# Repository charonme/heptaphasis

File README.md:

# [heptaphasis](http://charon.sk/heptaphasis)
### 7-phase quadrature sine LFO for eurorack
based on [Yusynth Quadrature VC-LFO](http://yusynth.net/Modular/EN/QUAD-LFO/index.html)

[Muffwiggler thread](https://www.muffwiggler.com/forum/viewtopic.php?t=215780)

<dl>
<dt>Frequency range</dt><dd>19 Hz - 0.0008 Hz (20 min)</dd>
<dt>Output phases</dt><dd>0&deg;, 45&deg;, 90&deg;, 135&deg;, 180&deg;, 225&deg;, 270&deg;</dd>
<dt>Amplitude</dt><dd>+-5V (10Vpp)</dd>
<dt>Power draw</dt><dd>+30mA, -27mA (depends on used LEDs)</dd>
<dt>Startup stabilisation</dt><dd>7 sec</dd>
<dt>PCB size</dt><dd>100x45.2mm</dd>
</dl>

[BOM](http://charon.sk/heptaphasis/#bom) / [Mouser project](https://www.mouser.com/ProjectManager/ProjectDetail.aspx?AccessID=b96a90f5ef)

---

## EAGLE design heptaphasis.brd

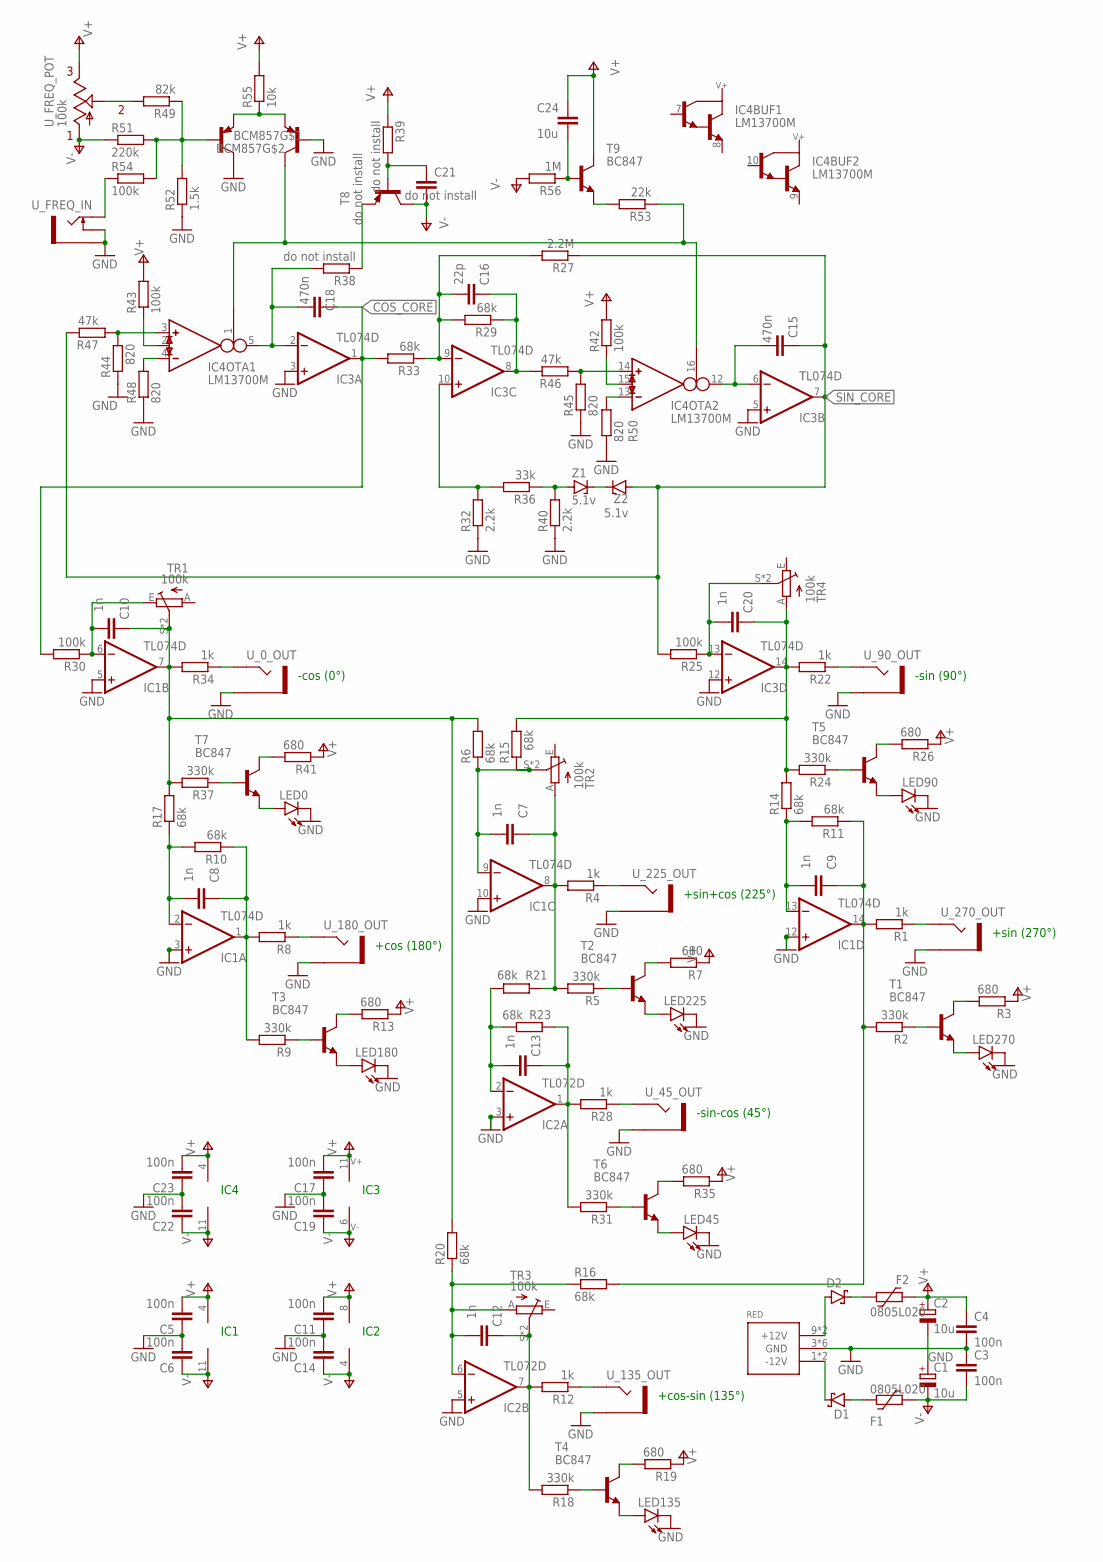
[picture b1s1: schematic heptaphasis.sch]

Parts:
BCM857: BCM857DS; SOT457R_PHILIPS
C1, C2: 10u; E2-5
C3, C4, C5, C6, C11, C14, C17, C19, C22, C23: 100n; C0805
C7, C8, C9, C10, C12, C13, C20: 1n; C0805
C15, C18: 470n; C0805
C16: 22p; C0805
C21: do not install; C0805
C24: 10u; C0805
D1, D2: VERTICAL_SCHOTTKY; DO41-7
F1, F2: 0805L020; 0805L
IC1, IC3: TL074D; SO14
IC2: TL072D; SO08
IC4: LM13700M; SO16
LED0, LED45, LED90, LED135, LED180, LED225, LED270: LED3MM
R1, R4, R8, R12, R22, R28, R34: 1k; R0805
R2, R5, R9, R18, R24, R31, R37: 330k; R0805
R3, R7, R13, R19, R26, R35, R41: 680; R0805
R6, R10, R11, R14, R15, R16, R17, R20, R21, R23, R29, R33: 68k; R0805
R25, R30, R42, R43, R54: 100k; R0805
R27: 2.2M; R0805
R32, R40: 2.2k; R0805
R36: 33k; R0805
R38, R39: do not install; R0805
R44, R45, R48, R50: 820; R0805
R46, R47: 47k; R0805
R49: 82k; R0805
R51: 220k; R0805
R52: 1.5k; R0805
R53: 22k; R0805
R55: 10k; R0805
R56: 1M; R0805
RED: POWER_SIMPLE10; POWER_10
T1, T2, T3, T4, T5, T6, T7, T9: BC847; SOT23
T8: do not install; SOT23
TR1, TR2, TR3, TR4: 100k; S64YW
U_0_OUT, U_45_OUT, U_90_OUT, U_135_OUT, U_180_OUT, U_225_OUT, U_270_OUT: PJ302M_NO_NORM
U_FREQ_IN: PJ302M
U_FREQ_POT: 100k; RK097-SINGLE-ELEMENT
Z1, Z2: 5.1v; SOD80C

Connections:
0OUT: R34.1, U_0_OUT.TIP
45OUT: R28.1, U_45_OUT.TIP
90OUT: R22.1, U_90_OUT.TIP
135OUT: R12.1, U_135_OUT.TIP
180OUT: R8.1, U_180_OUT.TIP
225OUT: R4.1, U_225_OUT.TIP
270OUT: R1.1, U_270_OUT.TIP
+12DIODE_FUSE: D2.C, F2.2
+12SUPPLY: D2.A, RED.9 (+12V), RED.10 (+12V)
-12DIODE_FUSE: D1.A, F1.2
-12SUPPLY: D1.C, RED.1 (-12V), RED.2 (-12V)
BUF0OUT: C10.1, IC1.7 (OUT), R6.2, R17.2, R20.2, R34.2, R37.2, TR1.S, TR1.S@1 (S)
BUF0_IN: C10.2, IC1.6 (-IN), R30.1, TR1.E
BUF45OUT: C13.1, IC2.1 (OUT), R23.1, R28.2, R31.2
BUF45_IN: C13.2, IC2.2 (-IN), R21.1, R23.2
BUF90OUT: C20.1, IC3.14 (OUT), R14.2, R15.2, R22.2, R24.2, TR4.A
BUF90_IN: C20.2, IC3.13 (-IN), R25.1, TR4.S, TR4.S@1 (S)
BUF135OUT: C12.1, IC2.7 (OUT), R12.2, R18.2, TR3.S, TR3.S@1 (S)
BUF135_IN: C12.2, IC2.6 (-IN), R16.1, R20.1, TR3.A
BUF180OUT: C8.1, IC1.1 (OUT), R8.2, R9.2, R10.1
BUF180_IN: C8.2, IC1.2 (-IN), R10.2, R17.1
BUF225OUT: C7.1, IC1.8 (OUT), R4.2, R5.2, R21.2, TR2.A
BUF225_IN: C7.2, IC1.9 (-IN), R6.1, R15.1, TR2.S, TR2.S@1 (S)
BUF270OUT: C9.1, IC1.14 (OUT), R1.2, R2.2, R11.1, R16.2
BUF270_IN: C9.2, IC1.13 (-IN), R11.2, R14.1
COS_CORE: C18.1, IC3.1 (OUT), R30.2, R33.2
COS_INTEG_IN: C18.2, IC3.2 (-IN), IC4.5 (OUT), R38.2
COS_OTA1_IN+: IC4.3 (IN_P), R44.2, R47.1
COS_OTA1_NEGATIVE: IC4.4 (IN_N), R48.2
EXP_EMITTERS: BCM857.1 (E), BCM857.4 (E), R55.1
FREQ_CURRENT: BCM857.3 (C), IC4.1 (I_BIAS), IC4.16 (I_BIAS), R53.1
FREQ_CV_IN: R54.1, U_FREQ_IN.TIP
FREQ_EXP_IN: BCM857.2 (B), R49.1, R51.2, R52.2, R54.2
FREQ_POT: R49.2, U_FREQ_POT.P$5 (S)
GND: BCM857.5 (B), BCM857.6 (C), C1.+, C2.-, C3.1, C4.2, C5.1, C6.2, C11.1, C14.2, C17.1, C19.2, C22.2, C23.1, IC1.3 (+IN), IC1.5 (+IN), IC1.10 (+IN), IC1.12 (+IN), IC2.3 (+IN), IC2.5 (+IN), IC3.3 (+IN), IC3.5 (+IN), IC3.12 (+IN), LED0.K (C), LED45.K (C), LED90.K (C), LED135.K (C), LED180.K (C), LED225.K (C), LED270.K (C), R32.1, R40.1, R44.1, R45.1, R48.1, R50.1, R52.1, RED.3 (GND), RED.4 (GND), RED.5 (GND), RED.6 (GND), RED.7 (GND), RED.8 (GND), U_0_OUT.GND (SLEEVE), U_45_OUT.GND (SLEEVE), U_90_OUT.GND (SLEEVE), U_135_OUT.GND (SLEEVE), U_180_OUT.GND (SLEEVE), U_225_OUT.GND (SLEEVE), U_270_OUT.GND (SLEEVE), U_FREQ_IN.GND (SLEEVE), U_FREQ_IN.SW (SWITCH)
HP_SUM: C16.1, IC3.8 (OUT), R29.1, R46.2
LED0+: LED0.A, T7.2 (E)
LED0PWR: R41.2, T7.3 (C)
LED0SIG: R37.1, T7.1 (B)
LED45+: LED45.A, T6.2 (E)
LED45PWR: R35.2, T6.3 (C)
LED45SIG: R31.1, T6.1 (B)
LED90+: LED90.A, T5.2 (E)
LED90PWR: R26.2, T5.3 (C)
LED90SIG: R24.1, T5.1 (B)
LED135+: LED135.A, T4.2 (E)
LED135PWR: R19.2, T4.3 (C)
LED135SIG: R18.1, T4.1 (B)
LED180+: LED180.A, T3.2 (E)
LED180PWR: R13.2, T3.3 (C)
LED180SIG: R9.1, T3.1 (B)
LED225+: LED225.A, T2.2 (E)
LED225PWR: R7.2, T2.3 (C)
LED225SIG: R5.1, T2.1 (B)
LED270+: LED270.A, T1.2 (E)
LED270PWR: R3.2, T1.3 (C)
LED270SIG: R2.1, T1.1 (B)
LINEARIZING1: IC4.2 (I_DIODE), R43.1
LINEARIZING2: IC4.15 (I_DIODE), R42.1
NEG_FDBK: C16.2, IC3.9 (-IN), R27.2, R29.2, R33.1
SIN_CORE: C15.1, IC3.7 (OUT), R25.2, R27.1, R47.2, Z2.A
SIN_FEEDBACK: IC3.10 (+IN), R32.2, R36.2
SIN_INTEG_IN: C15.2, IC3.6 (-IN), IC4.12 (OUT)
SIN_OTA2_IN+: IC4.14 (IN_P), R45.2, R46.1
SIN_OTA2_NEGATIVE: IC4.13 (IN_N), R50.2
START_AMP_EMIT: R38.1, T8.2 (E)
START_AMP_GATE: C21.1, R39.2, T8.1 (B)
START_FREQ_EMIT: R53.2, T9.2 (E)
START_FREQ_GATE: C24.2, R56.1, T9.1 (B)
V+: C2.+, C4.1, C5.2, C11.2, C17.2, C23.2, C24.1, F2.1, IC1.4 (V+), IC2.8 (V+), IC3.4 (V+), IC4.11 (V+), R3.1, R7.1, R13.1, R19.1, R26.1, R35.1, R39.1, R41.1, R42.2, R43.2, R55.2, T9.3 (C), U_FREQ_POT.P$4 (E)
V-: C1.-, C3.2, C6.1, C14.1, C19.1, C21.2, C22.1, F1.1, IC1.11 (V-), IC2.4 (V-), IC3.11 (V-), IC4.6 (V-), R51.1, R56.2, T8.3 (C), U_FREQ_POT.P$6 (A)
ZENERS_CATHODES: Z1.C, Z2.C
ZENER_ANODE: R36.1, R40.2, Z1.A

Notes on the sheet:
-cos (0°)
+cos (180°)
+sin (270°)
-sin (90°)
-sin-cos (45°)
+sin+cos (225°)
+cos-sin (135°)
IC1
IC3
IC4
IC2

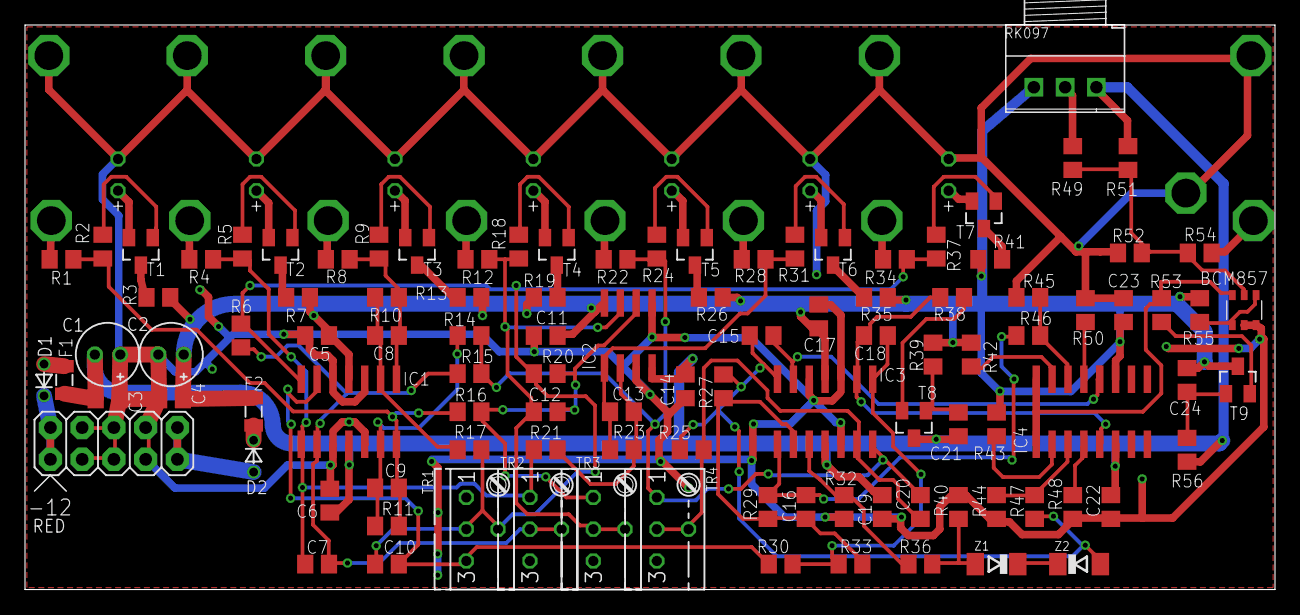
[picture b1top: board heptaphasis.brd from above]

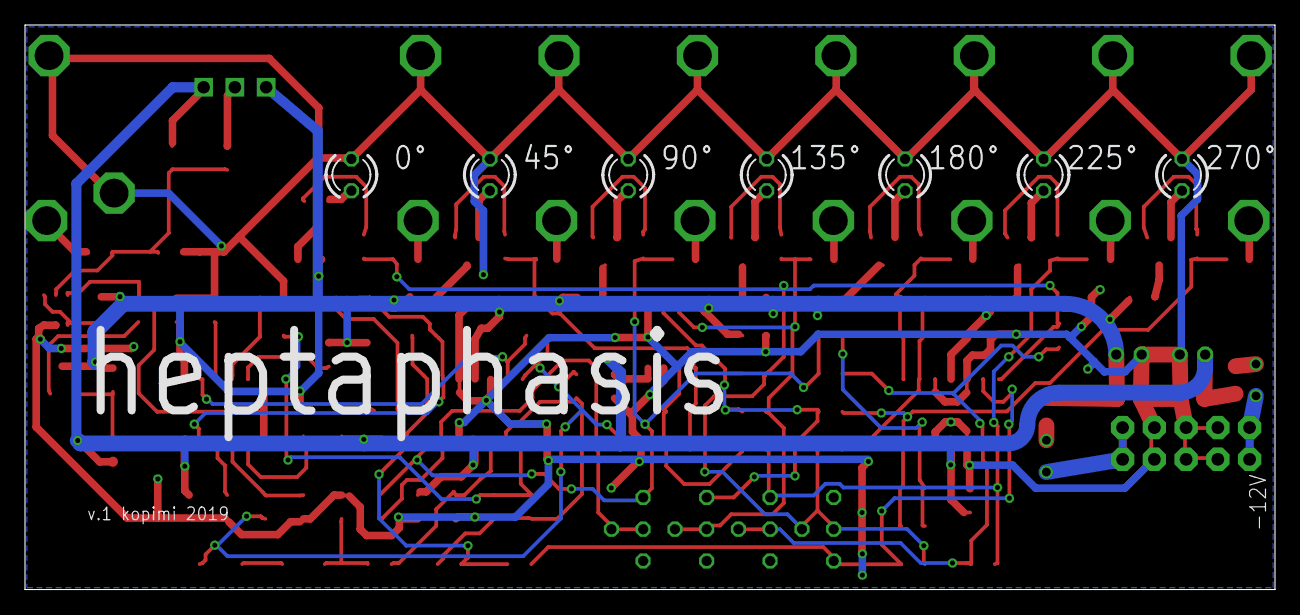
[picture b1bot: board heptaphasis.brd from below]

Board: 2 copper layers, 100.0 x 45.2 mm, 121 parts (7 on the bottom side), 73 nets.
